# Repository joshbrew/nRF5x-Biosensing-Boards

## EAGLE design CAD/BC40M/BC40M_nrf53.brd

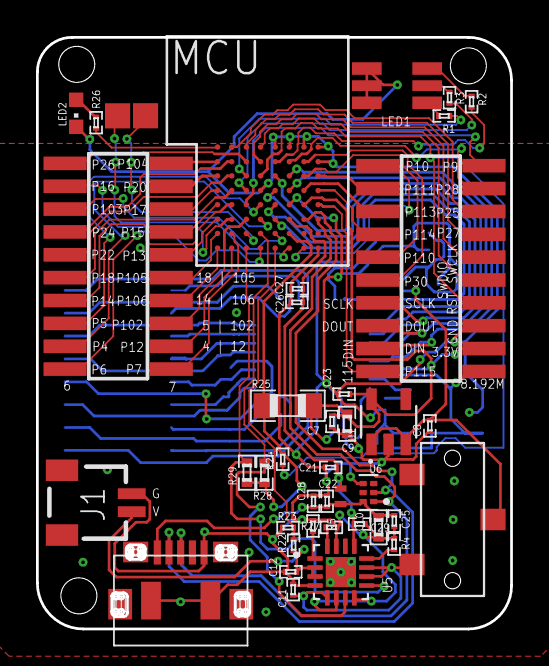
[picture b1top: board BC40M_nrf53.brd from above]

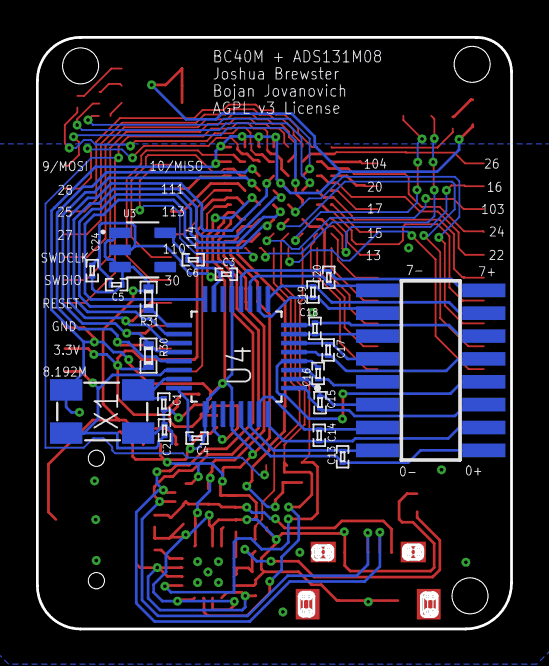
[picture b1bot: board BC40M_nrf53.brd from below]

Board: 2 copper layers, 26.3 x 32.9 mm, 62 parts (21 on the bottom side), 86 nets.

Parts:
C1, C2: 10pF; 0201
C3, C5, C6, C7, C8, C10, C24: 1uF; 0201
C4: 220nF; 0201
C9, C29: 10uF; 0402
C11, C12, C25, C26: 4.7uF; 0201
C13, C14, C15, C16, C17, C18, C19, C20: 100pF; 0201
C21, C23, C27, C28: 0.1uF; 0201
C22: 10nF; 0201
HDR1, HDR2: 1365-20
I1: 120Ω/500mAh; 0402_COILCRAFT
J1: SM02B-SRSS-TB(LF)(SN)
LED1: GM5WA94310A
LED2: CHIPLED_0603
MCU: BC40M
NFC1, NFC2: TPTP14SQ; TP14SQ
R1, R2, R3, R26: 3.3kΩ; 0201
R4: 1.18kΩ; 0201
R5: 1.13kΩ; 0201
R22: 348kΩ; 0201
R23: 750kΩ; 0201
R24: 100kΩ; 0201
R25: 0Ω; 0805
R27: 10kΩ; 0201
R28, R29: 10kΩ; 0402
R30, R31: 100kΩ; 0402
S1: CL-SB-12B-01T; CL-SB-12B
U1, U3: LP5907MFX-3.3/NOPB; SOT95P280X145-5N
U2: DX4R005JJ2R1800
U4: ADS131M08IPBS; QFP50P700X700X120-32N
U5: BQ24072RGTR; QFN50P300X300X100-17N
U6: TPD4S012DRYR; PSON50P145X100X60-6N
X1: ABM3B-8.000MHZ-B2-T
X5: 1365-16

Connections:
0N: C13.2, U4.30, X5.2
0P: C13.1, U4.29, X5.1
1N: C14.2, U4.31, X5.4
1P: C14.1, U4.32, X5.3
2N: C15.2, U4.2, X5.6
2P: C15.1, U4.1, X5.5
3N: C16.2, U4.3, X5.8
3P: C16.1, U4.4, X5.7
4N: C17.2, U4.6, X5.10
4P: C17.1, U4.5, X5.9
5N: C18.2, U4.7, X5.12
5P: C18.1, U4.8, X5.11
6N: C19.2, U4.10, X5.14
6P: C19.1, U4.9, X5.13
7N: C20.2, U4.11, X5.16
7P: C20.1, U4.12, X5.15
+5V: C22.2, C25.2, C28.2, C29.2, I1.P$2, U2.1, U6.6
+5V_ISO: C10.2, C21.1, C26.2, C27.2, I1.P$1, MCU.F5, U5.13
AVDD: C3.2, C6.1, U3.5, U4.15
BAT: C12.2, J1.2, R22.1, U5.2, U5.3
CAP: C4.1, U4.24
CHG: MCU.C7, R29.2, U5.9
CLKIN: C1.1, U4.23, X1.1
CLKOUT: C2.1, HDR2.20, U4.22, X1.3
CS: MCU.E4, R31.1, U4.17
CUR_DETECT: MCU.E7, R22.2, R23.1
D+: MCU.H5, U2.3, U6.1
D-: MCU.G5, U2.2, U6.2
DIN: HDR2.17, MCU.F2, U4.21
DOUT: HDR2.15, MCU.F3, R30.1, U4.20
DRDY: MCU.E3, U4.18
GND: C1.2, C2.2, C3.1, C4.2, C5.2, C6.2, C7.1, C8.1, C9.1, C10.1, C11.1, C12.1, C21.2, C22.1, C23.1, C24.1, C25.1, C26.1, C27.1, C28.1, C29.1, HDR2.16, J1.1, LED1.4, LED1.5, LED1.6, LED2.C, MCU.D3, MCU.E0, MCU.F0, MCU.F4, MCU.G0, MCU.H0, MCU.H1, MCU.H7, R4.1, R5.1, R23.2, R27.1, U1.2, U2.5, U2.MP1, U2.MP2, U3.2, U4.13, U4.25, U4.28, U5.4, U5.6, U5.8, U5.15, U6.4, X1.2, X1.4
ILM: R4.2, U5.12
ISET: R5.2, U5.16
LED5: LED2.A, R26.2
unnamed: LED1.2, R3.2
unnamed: LED1.3, R2.2
unnamed: LED1.1, R1.2
NFC1: MCU.F7, NFC2.TP
NFC2: MCU.C6, NFC1.TP
P4_AIN0: HDR1.17, MCU.D5
P5_AIN1: HDR1.15, MCU.D4
P6_AIN2: HDR1.19, MCU.D7
P7_AIN3: HDR1.20, MCU.B6
P9_MOSI: HDR2.2, MCU.C4
P10_MISO: HDR2.1, MCU.G7
P12: HDR1.18, MCU.B7
P13: HDR1.10, MCU.A5
P14: HDR1.13, MCU.B4
P15: HDR1.8, MCU.A4
P16: HDR1.3, MCU.B5
P17: HDR1.6, MCU.A3
P18: HDR1.11, MCU.B3
P19: MCU.C3, R3.1
P20: HDR1.4, MCU.A2
P21: MCU.C2, R1.1
P22: HDR1.9, MCU.B2
P24: HDR1.7, MCU.B1
P25_AIN4: HDR2.6, MCU.B0
P26_AIN5: HDR1.1, MCU.C1
P27_AIN6: HDR2.8, MCU.C0
P28_AIN7: HDR2.4, MCU.F1
P29: MCU.E1, R2.1
P30: HDR2.11, MCU.G1
P102: HDR1.16, MCU.C5
P103: HDR1.5, MCU.E6
P104: HDR1.2, MCU.A1
P105: HDR1.12, MCU.A6
P106: HDR1.14, MCU.A7
P109: MCU.A0, R26.1
P110: HDR2.9, MCU.G2
P111: HDR2.3, MCU.H2
P113: HDR2.5, MCU.G3
P114: HDR2.7, MCU.H3
P115: HDR2.19, MCU.H4
PGOOD: MCU.D6, R28.2, U5.7
RESET: HDR2.14, MCU.D2, R24.1
SCLK: HDR2.13, MCU.E2, U4.19
SWDCLK: HDR2.10, MCU.D1
SWDIO: HDR2.12, MCU.D0
SYNC/RESET: MCU.E5, U4.16
TS: R27.2, U5.1
VDD: C7.2, C9.2, C23.2, HDR2.18, MCU.G4, R25.2, R30.2, U1.5, U4.26
VDDH: MCU.F6, R24.2, R25.1, R28.1, R29.1
VIN: C5.1, C8.2, C24.2, R31.2, S1.2, U1.1, U1.3, U3.1, U3.3
VSWITCH: C11.2, S1.3, U5.5, U5.10, U5.11

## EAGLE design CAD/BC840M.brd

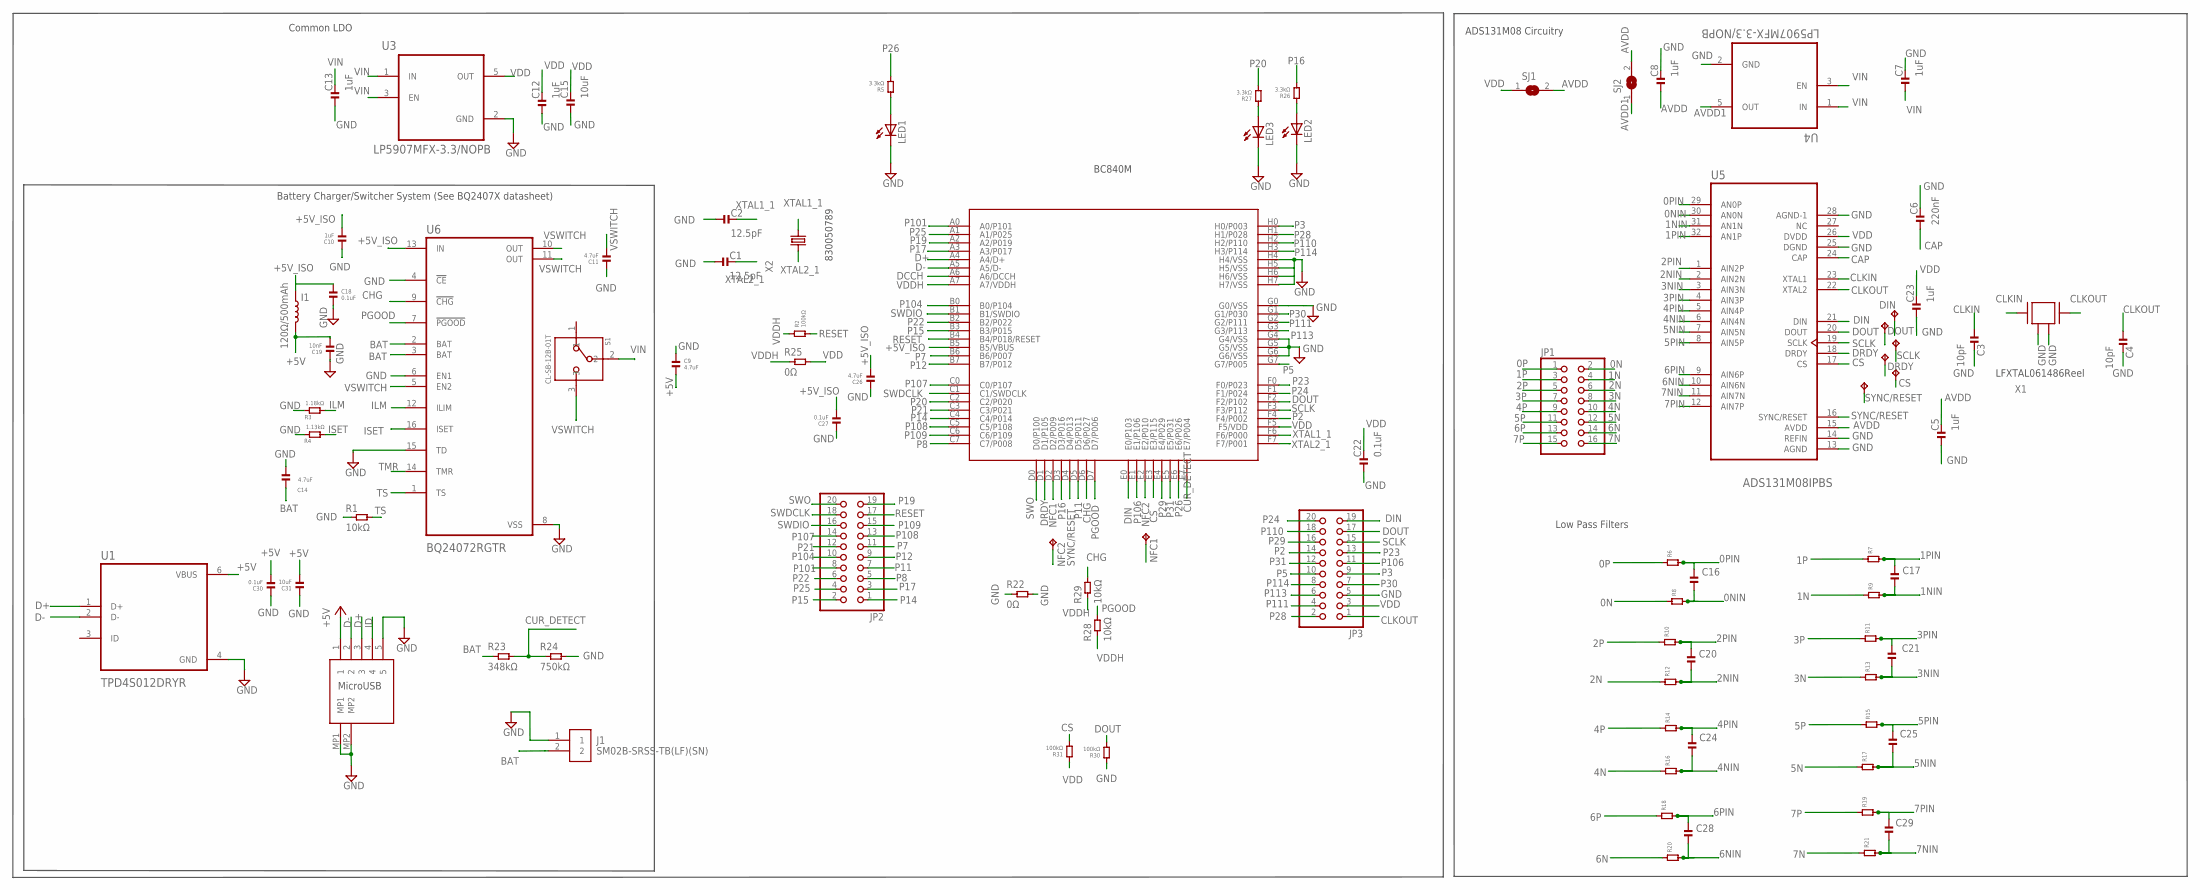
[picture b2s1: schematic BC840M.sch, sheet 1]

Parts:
C1, C2: 12.5pF; 0201
C3, C4: 10pF; 0201
C5, C7, C8, C10, C12, C13, C23: 1uF; 0201
C6: 220nF; 0201
C9, C11, C14, C26: 4.7uF; 0201
C15, C31: 10uF; 0402
C16, C17, C20, C21, C24, C25, C28, C29: 100pF; 0603
C18, C22, C27, C30: 0.1uF; 0201
C19: 10nF; 0201
CS: TPTP07R; TP07R
DIN: TPTP07R; TP07R
DOUT: TPTP07R; TP07R
DRDY: TPTP07R; TP07R
I1: 120Ω/500mAh; 0402_COILCRAFT
J1: SM02B-SRSS-TB(LF)(SN)
JP1: PINHD-2X8SMT; 2X08_SMT
JP2, JP3: PINHD-2X10SMT; 2X10_SMT
LED1, LED2, LED3: LEDCHIPLED_0603; CHIPLED_0603
NFC1, NFC2: TPTP14SQ; TP14SQ
R1: 10kΩ; 0201
R2: 100kΩ; 0201
R3: 1.18kΩ; 0603
R4: 1.13kΩ; 0603
R5, R26, R27: 3.3kΩ; 0201
R6, R7, R8, R9, R10, R11, R12, R13, R14, R15, R16, R17, R18, R19, R20, R21: 1MOhm; 0603
R22, R25: 0Ω; 0805
R23: 348kΩ; 0603
R24: 750kΩ; 0603
R28, R29: 10kΩ; 0402
R30, R31: 100kΩ; 0402
S1: CL-SB-12B-01T; CL-SB-12B
SCLK: TPTP07R; TP07R
SJ1, SJ2: SJ
SYNC: TPTP07R; TP07R
U1: TPD4S012DRYR; PSON50P145X100X60-6N
U2: BC840M
U3, U4: LP5907MFX-3.3/NOPB; SOT95P280X145-5N
U5: ADS131M08IPBS; QFP50P700X700X120-32N
U6: BQ24072RGTR; QFN50P300X300X100-17N
U7: DX4R005JJ2R1800
X1: ABM3B-8.000MHZ-B2-T
X2: FC-12M

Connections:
0N: JP1.2, R8.1
0NIN: C16.2, R8.2, U5.30 (AN0N)
0P: JP1.1, R6.1
0PIN: C16.1, R6.2, U5.29 (AN0P)
1N: JP1.4, R9.1
1NIN: C17.2, R9.2, U5.31 (AN1N)
1P: JP1.3, R7.1
1PIN: C17.1, R7.2, U5.32 (AN1P)
2N: JP1.6, R12.1
2NIN: C20.2, R12.2, U5.2 (AIN2N)
2P: JP1.5, R10.1
2PIN: C20.1, R10.2, U5.1 (AIN2P)
3N: JP1.8, R13.1
3NIN: C21.2, R13.2, U5.3 (AIN3N)
3P: JP1.7, R11.1
3PIN: C21.1, R11.2, U5.4 (AIN3P)
4N: JP1.10, R16.1
4NIN: C24.2, R16.2, U5.6 (AIN4N)
4P: JP1.9, R14.1
4PIN: C24.1, R14.2, U5.5 (AIN4P)
5N: JP1.12, R17.1
5NIN: C25.2, R17.2, U5.7 (AIN5N)
5P: JP1.11, R15.1
5PIN: C25.1, R15.2, U5.8 (AIN5P)
6N: JP1.14, R20.1
6NIN: C28.2, R20.2, U5.10 (AIN6N)
6P: JP1.13, R18.1
6PIN: C28.1, R18.2, U5.9 (AIN6P)
7N: JP1.16, R21.1
7NIN: C29.2, R21.2, U5.11 (AIN7N)
7P: JP1.15, R19.1
7PIN: C29.1, R19.2, U5.12 (AIN7P)
+5V: C9.2, C19.2, C30.2, C31.2, I1.P$2 (2), U1.6 (VBUS), U7.1
+5V_ISO: C10.2, C18.1, C26.2, C27.2, I1.P$1 (1), U2.B5 (B5/VBUS), U6.13 (IN)
AVDD: C5.2, C8.1, SJ1.2, SJ2.2, U5.15 (AVDD)
AVDD1: SJ2.1, U4.5 (OUT)
BAT: C14.2, J1.2, R23.1, U6.2 (BAT), U6.3 (BAT)
CAP: C6.1, U5.24 (CAP)
CHG: R29.2, U2.D6 (D6/P027), U6.9 (!CHG)
CLKIN: C3.1, U5.23 (XTAL1), X1.1
CLKOUT: C4.1, JP3.1, U5.22 (XTAL2), X1.3
CS: CS.TP, R31.1, U2.E3 (E3/P115), U5.17 (CS)
CUR_DETECT: R23.2, R24.1, U2.E7 (E7/P004)
D+: U1.1 (D+), U2.A4 (A4/D+), U7.3
D-: U1.2 (D-), U2.A5 (A5/D-), U7.2
DCCH: U2.A6 (A6/DCCH)
DIN: DIN.TP, JP3.19, U2.E0 (E0/P103), U5.21 (DIN)
DOUT: DOUT.TP, JP3.17, R30.1, U2.F2 (F2/P102), U5.20 (DOUT)
DRDY: DRDY.TP, U2.D1 (D1/P105), U5.18 (DRDY)
GND: C1.1, C2.1, C3.2, C4.2, C5.1, C6.2, C7.2, C8.2, C9.1, C10.1, C11.1, C12.1, C13.1, C14.1, C15.1, C18.2, C19.1, C22.1, C23.1, C26.1, C27.1, C30.1, C31.1, J1.1, JP3.5, LED1.C, LED2.C, LED3.C, R1.1, R3.1, R4.1, R22.1, R22.2, R24.2, R30.2, U1.4 (GND), U2.G0 (G0/VSS), U2.G4 (G4/VSS), U2.G5 (G5/VSS), U2.G6 (G6/VSS), U2.H4 (H4/VSS), U2.H5 (H5/VSS), U2.H6 (H6/VSS), U2.H7 (H7/VSS), U3.2 (GND), U4.2 (GND), U5.13 (AGND), U5.14 (REFIN), U5.25 (DGND), U5.28 (AGND-1), U6.4 (!CE), U6.6 (EN1), U6.8 (VSS), U6.15 (TD), U7.5, U7.MP1, U7.MP2, X1.2, X1.4
ID: U7.4
ILM: R3.2, U6.12 (ILIM)
ISET: R4.2, U6.16 (ISET)
LED1: LED1.A, R5.2
LED2: LED2.A, R26.2
LED3: LED3.A, R27.2
NFC1: NFC2.TP, U2.D2 (D2/P009)
NFC2: NFC1.TP, U2.E2 (E2/P010)
P2: JP3.14, U2.F4 (F4/P002)
P3: JP3.9, U2.H0 (H0/P003)
P5: JP3.10, U2.G7 (G7/P005)
P7: JP2.11, U2.B6 (B6/P007)
P8: JP2.5, U2.C7 (C7/P008)
P11: JP2.7, U2.D5 (D5/P011)
P12: JP2.9, U2.B7 (B7/P012)
P14: JP2.1, U2.C4 (C4/P014)
P15: JP2.2, U2.B3 (B3/P015)
P16: R26.1, U2.D3 (D3/P016)
P17: JP2.3, U2.A3 (A3/P017)
P19: JP2.19, U2.A2 (A2/P019)
P20: R27.1, U2.C2 (C2/P020)
P21: JP2.12, U2.C3 (C3/P021)
P22: JP2.6, U2.B2 (B2/P022)
P23: JP3.13, U2.F0 (F0/P023)
P24: JP3.20, U2.F1 (F1/P024)
P25: JP2.4, U2.A1 (A1/P025)
P26: R5.1, U2.E6 (E6/P026)
P28: JP3.2, U2.H1 (H1/P028)
P29: JP3.16, U2.E4 (E4/P029)
P30: JP3.7, U2.G1 (G1/P030)
P31: JP3.12, U2.E5 (E5/P031)
P101: JP2.8, U2.A0 (A0/P101)
P104: JP2.10, U2.B0 (B0/P104)
P106: JP3.11, U2.E1 (E1/P106)
P107: JP2.14, U2.C0 (C0/P107)
P108: JP2.13, U2.C5 (C5/P108)
P109: JP2.15, U2.C6 (C6/P109)
P110: JP3.18, U2.H2 (H2/P110)
P111: JP3.4, U2.G2 (G2/P111)
P113: JP3.6, U2.G3 (G3/P113)
P114: JP3.8, U2.H3 (H3/P114)
PGOOD: R28.2, U2.D7 (D7/P006), U6.7 (!PGOOD)
RESET: JP2.17, R2.1, U2.B4 (B4/P018/RESET)
SCLK: JP3.15, SCLK.TP, U2.F3 (F3/P112), U5.19 (SCLK)
SWDCLK: JP2.18, U2.C1 (C1/SWDCLK)
SWDIO: JP2.16, U2.B1 (B1/SWDIO)
SWO: JP2.20, U2.D0 (D0/P100)
SYNC/RESET: SYNC.TP, U2.D4 (D4/P013), U5.16 (SYNC/RESET)
TMR: U6.14 (TMR)
TS: R1.2, U6.1 (TS)
VDD: C12.2, C15.2, C22.2, C23.2, JP3.3, R25.2, R31.2, SJ1.1, U2.F5 (F5/VDD), U3.5 (OUT), U5.26 (DVDD)
VDDH: R2.2, R25.1, R28.1, R29.1, U2.A7 (A7/VDDH)
VIN: C7.1, C13.2, S1.2, U3.1 (IN), U3.3 (EN), U4.1 (IN), U4.3 (EN)
VSWITCH: C11.2, S1.3, U6.5 (EN2), U6.10 (OUT), U6.11 (OUT)
XTAL1_1: C2.2, U2.F6 (F6/P000), X2.2
XTAL2_1: C1.2, U2.F7 (F7/P001), X2.1

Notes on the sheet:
LFXTAL061486Reel
830050789
MicroUSB
Battery Charger/Switcher System (See BQ2407X datasheet)
ADS131M08 Circuitry
Common LDO
BC840M
Low Pass Filters

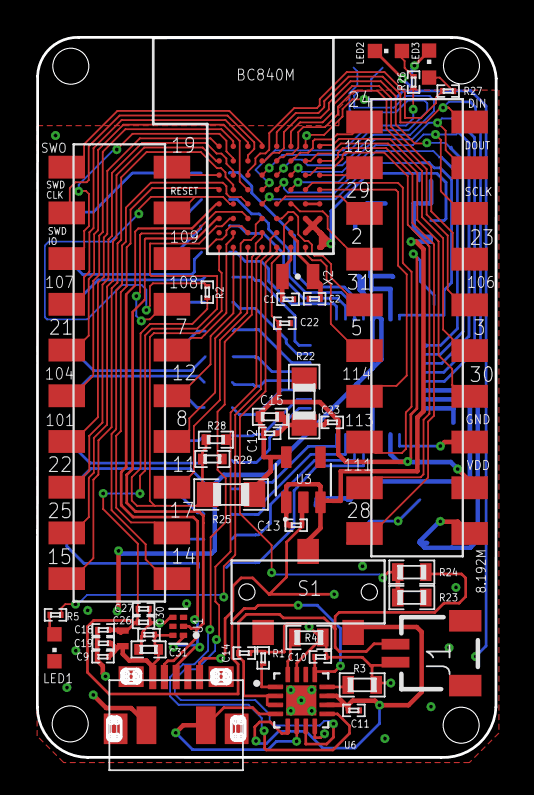
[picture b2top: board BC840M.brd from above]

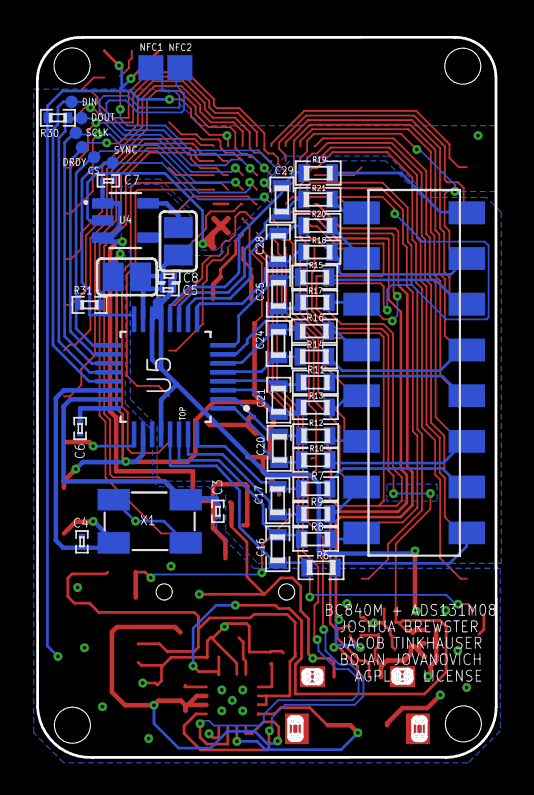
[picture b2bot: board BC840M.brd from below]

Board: 2 copper layers, 25.5 x 40.0 mm, 90 parts (46 on the bottom side), 103 nets.

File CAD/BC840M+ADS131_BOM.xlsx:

Designators | Ct | Part # | Description | Substitutes | Cost | 1.0 | 10.0 | 100.0 | 1000.0
U1 | 1.0 | TPD4S012DRYR | TVS Diodes |  |  | 0.73 | 6.48 | 49.7 | 314.0
U2 | 1.0 | BC840M | Fanstel Microcontroller |  | From Fanstel: | 8.86 | 84.9 | 812.0 | 7380.0
U3,U4 | 2.0 | LP5907-3.3MFX | 3v3 LDO | Stock (moq 155) |  | 0.7 | 5.93 | 41.1 | 269.0
U5 | 1.0 | ADS131M08IPBS | ADC 24bit 8ch |  | From TI: | 7.739 | 77.39 | 630.9 | 4206
U6 | 1.0 | BQ24076RGTR | Battery charge/switch interface | BQ2407xRGTR |  | 2.52 | 22.7 | 183.0 | 1250.0
U7 | 1.0 | DX4R005JJ2R1800 | MicroUSB port |  |  | 0.79 | 6.32 | 54.9 | 386.0
S1 | 1.0 | CL-SB-12B-01T | Switch On-Off | Alt part/source |  | 0.93 | 8.37 | 66.1 | 533.0
X1 | 1.0 | LFXTAL061486Reel | 8.192Mhz Crystal |  |  | 0.92 | 7.63 | 67.5 | 516.0
X2 | 1.0 | 8.30105946101E11 | 32.7680 Crystal |  |  | 0.67 | 6.11 | 52.4 | 524
I1 | 1.0 | MMZ1005S121CT000 | 120Ohm/500mAh 0402 INDUCTOR |  |  | 0.1 | 0.54 | 2.9 | 23.0
C1,C2 | 2.0 | CC0201DRNPO9BN7R0 | 7pF 0201 MLCC |  |  | 0.1 | 0.37 | 1.8 | 10.0
C3,C4, | 2.0 | 02015A100JAT2A | 10pF 0201 MLCC |  |  | 0.1 | 0.37 | 1.8 | 10.0
C5,C7,C8,C10,C12,C13,C23 | 7.0 | 02016D224KAT2A | 1uF 0201 MLCC |  |  | 0.1 | 0.37 | 1.8 | 10.0
C6 | 1.0 | 02016D224KAT2A | 220nF 0201 MLCC |  |  | 0.1 | 0.37 | 1.8 | 10.0
C9,C11,C14,C26 | 4.0 | AMK063EBJ475MP-F | 4.7uF 0201 MLCC |  |  | 0.1 | 0.37 | 1.8 | 10.0
C15,C31 | 2.0 | 0402YG104ZAT4A | 10uF 0402 MLCC |  |  | 0.1 | 0.37 | 1.8 | 10.0
C18,C22,C27,C30 | 4.0 | 0201ZD104KAT2A | 0.1uF 0201 MLCC |  |  | 0.1 | 0.37 | 1.8 | 10.0
C19 | 1.0 | 0201YD103KAT4A | 10nF 0201 MLCC |  |  | 0.1 | 0.37 | 1.8 | 10.0
C16,C17,C20,C21,C24,C25,C28,C29 | 8.0 | 06035A101JAT4A | 100pF 0603 MLCC | 1uF 0603 MLCC |  | 0.1 | 0.37 | 1.8 | 10.0
R6,R7,R8,R9,R10,R11,R12,R13,R1,R15,R16,R17,R18,R19,R20 | 16.0 | AC0603JR-071ML | 1MOhm 0603 RESISTOR | 100k 0603 RESISTOR |  | 0.1 | 0.2 | 4.8 | 8.0
R1 | 1.0 | CRCW020110K0JNED | 10KOhm 0201 RESISTOR |  |  | 0.1 | 0.2 | 4.8 | 8.0
R28, R29 | 2.0 | AC0402FR-0710KL | 10KOhm 0402 RESISTOR |  |  | 0.1 | 0.2 | 4.8 | 8.0
R2 | 1.0 | CRCW0201100KFNED | 100KOhm 0201 RESISTOR |  |  | 0.1 | 0.2 | 4.8 | 8.0
R30,R31 | 2.0 | AC0402FR-13100KL | 100KOhm 0402 RESISTOR |  |  | 0.1 | 0.2 | 4.8 | 8.0
R23 | 1.0 | RC0603FR-07348KL | 348KOhm 0603 RESISTOR |  |  | 0.1 | 0.2 | 4.8 | 8.0
R24 | 1.0 | CR0603-FX-7503ELF | 750KOhm 0603 RESISTOR |  |  | 0.1 | 0.2 | 4.8 | 8.0
R5,R26,R27 | 3.0 | RC0201FR-073K3L | 3.3KOhm 0201 RESISTOR |  |  | 0.1 | 0.2 | 4.8 | 8.0
R3 | 1.0 | RC0603FR-071K18L | 1.18KOhm 0603 RESISTOR |  |  | 0.1 | 0.2 | 4.8 | 8.0
R4 | 1.0 | CR0603-FX-1131ELF | 1.13KOhm 0603 RESISTOR |  |  | 0.1 | 0.2 | 4.8 | 8.0
R22,R25 | 2.0 | RC0805JR-070RL | 0Ohm 0805 RESISTOR |  |  | 0.1 | 0.2 | 4.8 | 8.0
JP1 | 1.0 | SSM-108-F-DV-K-TR | 2X8 SMT 2.54MM HEADER FEMALE |  |  | 3.75 | 36.0 | 300.0 | 2170.0
JP2,JP3 | 2.0 | SSM-110-F-DV-P-TR | 2X10 SMT 2.54MM HEADER FEMALE |  |  | 4.12 | 39.6 | 330.0 | 2390.0
LED1 | 1.0 | AA1608SESK | 0603 CHIPLED ORANGE |  |  | 0.48 | 2.81 | 16.2 | 127.0
LED2 | 1.0 | AA1608QBS/D-10MAV | 0603 CHIPLED BLUE |  |  | 0.48 | 2.81 | 16.2 | 127.0
LED3 | 1.0 | AA1608ZGSK-10MAV | 0603 CHIPLED GREEN |  |  | 0.46 | 2.96 | 22.8 | 151.0
J1 | 1.0 | SM02B-SRSS-TB(LF)(SN) | CONN HEADER SH 2POS 1MM |  | Win-Source: (moq 135) | 1.0 | 10.0 | 51.74 | 301.125
 |  |  |  |  |  | 36.249 | 326.08 | 2766.44 | 20845.125
 |  | SHR-02V-S | CONN HOUSING SH 2POS 1MM | Stock? or Stock? | Unit Cost | 36.249 | 32.608 | 27.6644 | 20.845125
 |  |  |  |  | W/out headers | 28.379 | 250.48 | 2136.44 | 16285.125
 |  |  |  |  | Unit Cost (not accurate) | 28.379 | 25.048 | 21.3644 | 16.285125

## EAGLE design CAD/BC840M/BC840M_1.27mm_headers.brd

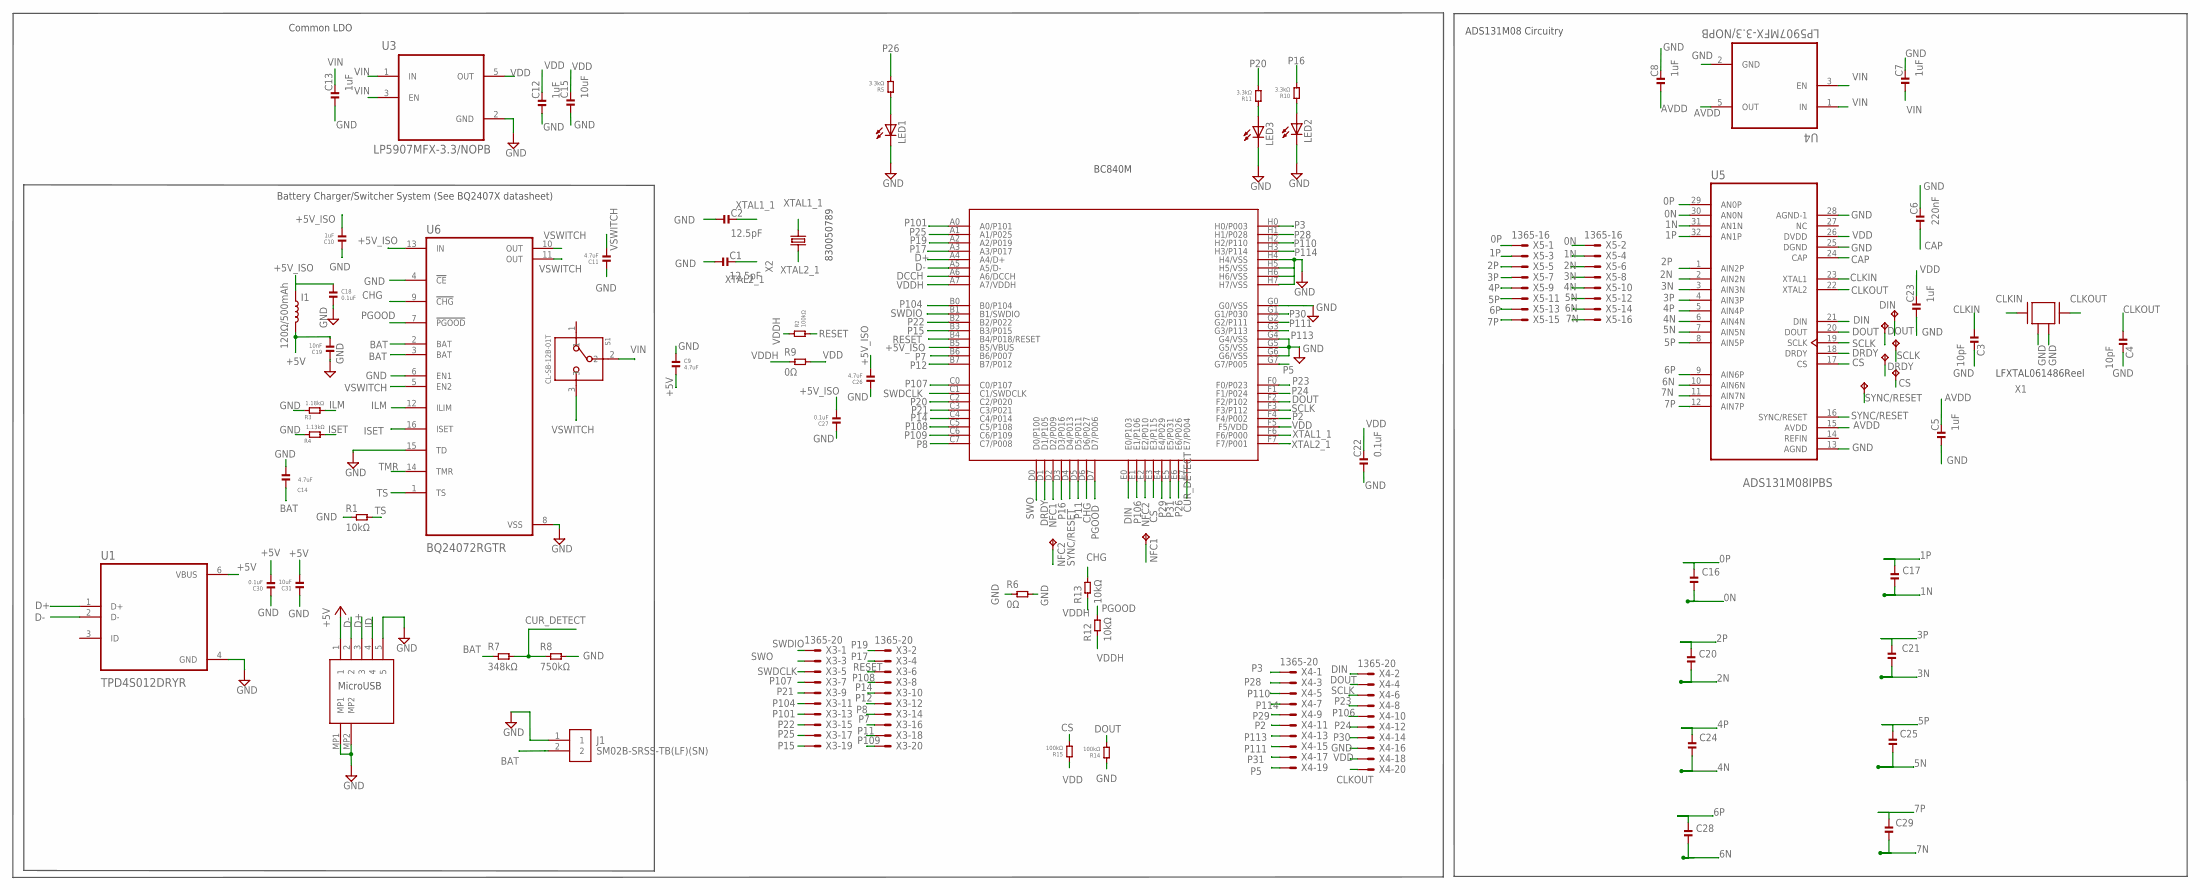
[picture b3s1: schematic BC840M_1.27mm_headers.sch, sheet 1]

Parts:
C1, C2: 12.5pF; 0201
C3, C4: 10pF; 0201
C5, C7, C8, C10, C12, C13, C23: 1uF; 0201
C6: 220nF; 0201
C9, C11, C14, C26: 4.7uF; 0201
C15, C31: 10uF; 0402
C16, C17, C20, C21, C24, C25, C28, C29: 100pF; 0201
C18, C22, C27, C30: 0.1uF; 0201
C19: 10nF; 0201
CS: TPTP07R; TP07R
DIN: TPTP07R; TP07R
DOUT: TPTP07R; TP07R
DRDY: TPTP07R; TP07R
I1: 120Ω/500mAh; 0402_COILCRAFT
J1: SM02B-SRSS-TB(LF)(SN)
LED1, LED2, LED3: LEDCHIPLED_0603; CHIPLED_0603
NFC1, NFC2: TPTP14SQ; TP14SQ
R1: 10kΩ; 0201
R2: 100kΩ; 0201
R3: 1.18kΩ; 0201
R4: 1.13kΩ; 0201
R5, R10, R11: 3.3kΩ; 0201
R6, R9: 0Ω; 0805
R7: 348kΩ; 0201
R8: 750kΩ; 0201
R12, R13: 10kΩ; 0402
R14, R15: 100kΩ; 0402
S1: CL-SB-12B-01T; CL-SB-12B
SCLK: TPTP07R; TP07R
SYNC: TPTP07R; TP07R
U1: TPD4S012DRYR; PSON50P145X100X60-6N
U2: BC840M
U3, U4: LP5907MFX-3.3/NOPB; SOT95P280X145-5N
U5: ADS131M08IPBS; QFP50P700X700X120-32N
U6: BQ24072RGTR; QFN50P300X300X100-17N
U7: DX4R005JJ2R1800
X1: ABM3B-8.000MHZ-B2-T
X2: FC-12M
X3, X4: 1365-20
X5: 1365-16

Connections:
0N: C16.2, U5.30 (AN0N), X5.2
0P: C16.1, U5.29 (AN0P), X5.1
1N: C17.2, U5.31 (AN1N), X5.4
1P: C17.1, U5.32 (AN1P), X5.3
2N: C20.2, U5.2 (AIN2N), X5.6
2P: C20.1, U5.1 (AIN2P), X5.5
3N: C21.2, U5.3 (AIN3N), X5.8
3P: C21.1, U5.4 (AIN3P), X5.7
4N: C24.2, U5.6 (AIN4N), X5.10
4P: C24.1, U5.5 (AIN4P), X5.9
5N: C25.2, U5.7 (AIN5N), X5.12
5P: C25.1, U5.8 (AIN5P), X5.11
6N: C28.2, U5.10 (AIN6N), X5.14
6P: C28.1, U5.9 (AIN6P), X5.13
7N: C29.2, U5.11 (AIN7N), X5.16
7P: C29.1, U5.12 (AIN7P), X5.15
+5V: C9.2, C19.2, C30.2, C31.2, I1.P$2 (2), U1.6 (VBUS), U7.1
+5V_ISO: C10.2, C18.1, C26.2, C27.2, I1.P$1 (1), U2.B5 (B5/VBUS), U6.13 (IN)
AVDD: C5.2, C8.1, U4.5 (OUT), U5.15 (AVDD)
BAT: C14.2, J1.2, R7.1, U6.2 (BAT), U6.3 (BAT)
CAP: C6.1, U5.24 (CAP)
CHG: R13.2, U2.D6 (D6/P027), U6.9 (!CHG)
CLKIN: C3.1, U5.23 (XTAL1), X1.1
CLKOUT: C4.1, U5.22 (XTAL2), X1.3, X4.20
CS: CS.TP, R15.1, U2.E3 (E3/P115), U5.17 (CS)
CUR_DETECT: R7.2, R8.1, U2.E7 (E7/P004)
D+: U1.1 (D+), U2.A4 (A4/D+), U7.3
D-: U1.2 (D-), U2.A5 (A5/D-), U7.2
DCCH: U2.A6 (A6/DCCH)
DIN: DIN.TP, U2.E0 (E0/P103), U5.21 (DIN), X4.2
DOUT: DOUT.TP, R14.1, U2.F2 (F2/P102), U5.20 (DOUT), X4.4
DRDY: DRDY.TP, U2.D1 (D1/P105), U5.18 (DRDY)
GND: C1.1, C2.1, C3.2, C4.2, C5.1, C6.2, C7.2, C8.2, C9.1, C10.1, C11.1, C12.1, C13.1, C14.1, C15.1, C18.2, C19.1, C22.1, C23.1, C26.1, C27.1, C30.1, C31.1, J1.1, LED1.C, LED2.C, LED3.C, R1.1, R3.1, R4.1, R6.1, R6.2, R8.2, R14.2, U1.4 (GND), U2.G0 (G0/VSS), U2.G4 (G4/VSS), U2.G5 (G5/VSS), U2.G6 (G6/VSS), U2.H4 (H4/VSS), U2.H5 (H5/VSS), U2.H6 (H6/VSS), U2.H7 (H7/VSS), U3.2 (GND), U4.2 (GND), U5.13 (AGND), U5.25 (DGND), U5.28 (AGND-1), U6.4 (!CE), U6.6 (EN1), U6.8 (VSS), U6.15 (TD), U7.5, U7.MP1, U7.MP2, X1.2, X1.4, X4.16
ID: U7.4
ILM: R3.2, U6.12 (ILIM)
ISET: R4.2, U6.16 (ISET)
LED1: LED1.A, R5.2
LED2: LED2.A, R10.2
LED3: LED3.A, R11.2
NFC1: NFC2.TP, U2.D2 (D2/P009)
NFC2: NFC1.TP, U2.E2 (E2/P010)
P2: U2.F4 (F4/P002), X4.11
P3: U2.H0 (H0/P003), X4.1
P5: U2.G7 (G7/P005), X4.19
P7: U2.B6 (B6/P007), X3.16
P8: U2.C7 (C7/P008), X3.14
P11: U2.D5 (D5/P011), X3.18
P12: U2.B7 (B7/P012), X3.12
P14: U2.C4 (C4/P014), X3.10
P15: U2.B3 (B3/P015), X3.19
P16: R10.1, U2.D3 (D3/P016)
P17: U2.A3 (A3/P017), X3.4
P19: U2.A2 (A2/P019), X3.2
P20: R11.1, U2.C2 (C2/P020)
P21: U2.C3 (C3/P021), X3.9
P22: U2.B2 (B2/P022), X3.15
P23: U2.F0 (F0/P023), X4.8
P24: U2.F1 (F1/P024), X4.12
P25: U2.A1 (A1/P025), X3.17
P26: R5.1, U2.E6 (E6/P026)
P28: U2.H1 (H1/P028), X4.3
P29: U2.E4 (E4/P029), X4.9
P30: U2.G1 (G1/P030), X4.14
P31: U2.E5 (E5/P031), X4.17
P101: U2.A0 (A0/P101), X3.13
P104: U2.B0 (B0/P104), X3.11
P106: U2.E1 (E1/P106), X4.10
P107: U2.C0 (C0/P107), X3.7
P108: U2.C5 (C5/P108), X3.8
P109: U2.C6 (C6/P109), X3.20
P110: U2.H2 (H2/P110), X4.5
P111: U2.G2 (G2/P111), X4.15
P113: U2.G3 (G3/P113), X4.13
P114: U2.H3 (H3/P114), X4.7
PGOOD: R12.2, U2.D7 (D7/P006), U6.7 (!PGOOD)
RESET: R2.1, U2.B4 (B4/P018/RESET), X3.6
SCLK: SCLK.TP, U2.F3 (F3/P112), U5.19 (SCLK), X4.6
SWDCLK: U2.C1 (C1/SWDCLK), X3.5
SWDIO: U2.B1 (B1/SWDIO), X3.1
SWO: U2.D0 (D0/P100), X3.3
SYNC/RESET: SYNC.TP, U2.D4 (D4/P013), U5.16 (SYNC/RESET)
TMR: U6.14 (TMR)
TS: R1.2, U6.1 (TS)
VDD: C12.2, C15.2, C22.2, C23.2, R9.2, R15.2, U2.F5 (F5/VDD), U3.5 (OUT), U5.26 (DVDD), X4.18
VDDH: R2.2, R9.1, R12.1, R13.1, U2.A7 (A7/VDDH)
VIN: C7.1, C13.2, S1.2, U3.1 (IN), U3.3 (EN), U4.1 (IN), U4.3 (EN)
VSWITCH: C11.2, S1.3, U6.5 (EN2), U6.10 (OUT), U6.11 (OUT)
XTAL1_1: C2.2, U2.F6 (F6/P000), X2.2
XTAL2_1: C1.2, U2.F7 (F7/P001), X2.1

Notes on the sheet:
LFXTAL061486Reel
830050789
MicroUSB
Battery Charger/Switcher System (See BQ2407X datasheet)
ADS131M08 Circuitry
Common LDO
BC840M

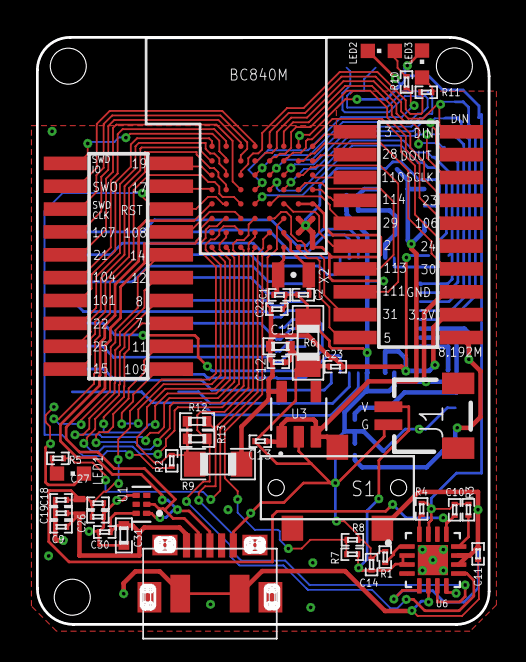
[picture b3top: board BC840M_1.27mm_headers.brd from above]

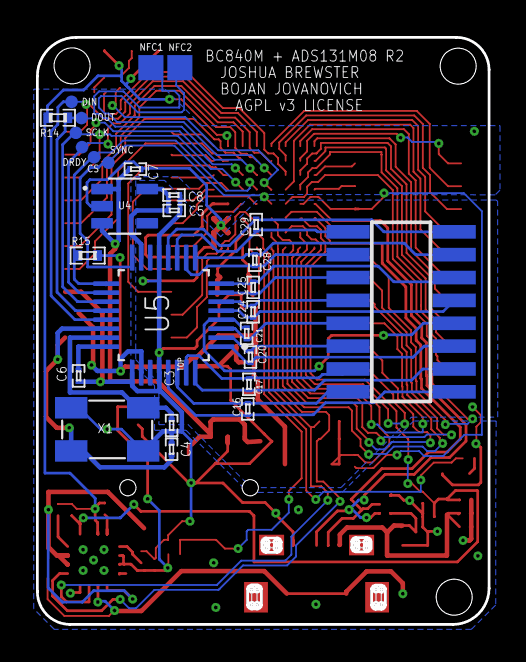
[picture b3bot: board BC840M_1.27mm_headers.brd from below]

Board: 2 copper layers, 25.1 x 32.6 mm, 72 parts (28 on the bottom side), 86 nets.

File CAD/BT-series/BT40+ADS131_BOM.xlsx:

Designators | Ct | Part # | Description | Substitutes | NOTES | Costs (old) | 1.0 | 10.0 | 100.0 | 1000.0
U1 | 1.0 | TPD4S012DRYR | TVS Diodes |  |  |  | 0.73 | 6.48 | 49.7 | 314.0
U2 | 1.0 | BT40 | Fanstel Microcontroller | BT840, BT832, BT832A, or variants (F, E, X, XE) | Prefer BT40 (nRF53) | From Fanstel: | 10.41 | 99.8 | 998.0 | 7650.0
U3,U4 | 2.0 | LP5907-3.3MFX | 3v3 LDO | Alt Stock (moq 155) |  |  | 0.7 | 5.93 | 41.1 | 269.0
U5 | 1.0 | ADS131M08IPBS | ADC 24bit 8ch |  |  | From TI: | 7.739 | 77.39 | 630.9 | 4206
U6 | 1.0 | BQ24076RGTR | Battery charge/switch interface | BQ2407xRGTR |  |  | 2.52 | 22.7 | 183.0 | 1250.0
U7 | 1.0 | DX4R005JJ2R1800 | MicroUSB port |  |  |  | 0.79 | 6.32 | 54.9 | 386.0
S1 | 1.0 | CL-SB-12B-01T | Switch On-Off | Alt part/source |  |  | 0.93 | 8.37 | 66.1 | 533.0
X1 | 1.0 | LFXTAL061486Reel | 8.192Mhz Crystal |  |  |  | 0.92 | 7.63 | 67.5 | 516.0
X2 | 1.0 | 8.30105946101E11 | 32.7680 Crystal |  |  |  | 0.67 | 6.11 | 52.4 | 524
I1 | 1.0 | MMZ1005S121CT000 | 120Ohm/500mAh 0402 INDUCTOR |  |  |  | 0.1 | 0.54 | 2.9 | 23.0
C1,C2 | 2.0 | CC0201DRNPO9BN7R0 | 7pF 0201 MLCC |  |  |  | 0.2 | 0.37 | 1.8 | 10.0
C3,C4, | 2.0 | 02015A100JAT2A | 10pF 0201 MLCC |  |  |  | 0.2 | 0.37 | 1.8 | 10.0
C5,C7,C8,C10,C12,C13,C23 | 7.0 | 02016D224KAT2A | 1uF 0201 MLCC |  |  |  | 0.7 | 0.37 | 1.8 | 10.0
C6 | 1.0 | 02016D224KAT2A | 220nF 0201 MLCC |  |  |  | 0.1 | 0.37 | 1.8 | 10.0
C9,C11,C14,C26 | 4.0 | AMK063EBJ475MP-F | 4.7uF 0201 MLCC |  |  |  | 0.4 | 1.48 | 7.2 | 40
C15,C31 | 2.0 | 0402YG104ZAT4A | 10uF 0402 MLCC |  |  |  | 0.2 | 0.74 | 3.6 | 20
C18,C22,C27,C30 | 4.0 | 0201ZD104KAT2A | 0.1uF 0201 MLCC |  |  |  | 0.4 | 1.48 | 7.2 | 40
C19 | 1.0 | 0201YD103KAT4A | 10nF 0201 MLCC |  |  |  | 0.8 | 2.96 | 14.4 | 80
C16,C17,C20,C21,C24,C25,C28,C29 | 8.0 | 02013C101KAT2A | 100pF 0201 MLCC |  |  |  | 0.1 | 0.37 | 1.8 | 10.0
R1 | 1.0 | CRCW020110K0JNED | 10KOhm 0201 RESISTOR |  |  |  | 0.2 | 0.2 | 4.8 | 8.0
R10, R11 | 2.0 | AC0402FR-0710KL | 10KOhm 0402 RESISTOR |  |  |  | 0.1 | 0.2 | 4.8 | 8.0
R2 | 1.0 | CRCW0201100KFNED | 100KOhm 0201 RESISTOR |  |  |  | 0.1 | 0.2 | 4.8 | 8.0
R12,R13 | 2.0 | AC0402FR-13100KL | 100KOhm 0402 RESISTOR |  |  |  | 0.1 | 0.2 | 4.8 | 8.0
R6 | 1.0 | RC0201FR-07348KL | 348KOhm 0201 RESISTOR |  |  |  | 0.1 | 0.2 | 4.8 | 8.0
R7 | 1.0 | RC0201FR-07750KL | 750KOhm 0201 RESISTOR |  |  |  | 0.1 | 0.2 | 4.8 | 8.0
R5,R8,R9 | 3.0 | RC0201FR-073K3L | 3.3KOhm 0201 RESISTOR |  |  |  | 0.1 | 0.2 | 4.8 | 8.0
R3 | 1.0 | RC0201FR-071K18L | 1.18KOhm 0201 RESISTOR |  |  |  | 0.1 | 0.2 | 4.8 | 8.0
R4 | 1.0 | ERJ-1GNF1131C | 1.13KOhm 0201 RESISTOR |  |  |  | 0.1 | 0.2 | 4.8 | 8.0
JP1 | 1.0 | NPTC082KFMS-RC | 2X8 SMT 1.25MM HEADER FEMALE |  |  |  | 1.89 | 16.41 | 146.66 | 1047.6
JP2,JP3 | 2.0 | NPTC102KFMS-RC | 2X10 SMT 1.25MM HEADER FEMALE
LED1 | 1.0 | AA1608SESK | 0603 CHIPLED ORANGE |  |  |  | 0.48 | 2.81 | 16.2 | 127.0
LED2 | 1.0 | AA1608QBS/D-10MAV | 0603 CHIPLED BLUE |  |  |  | 0.48 | 2.81 | 16.2 | 127.0
LED3 | 1.0 | AA1608ZGSK-10MAV | 0603 CHIPLED GREEN |  |  |  | 0.46 | 2.96 | 22.8 | 151.0
J1 | 1.0 | SM02B-SRSS-TB(LF)(SN) | CONN HEADER SH 2POS 1MM
total | 62 |  |  |  |  |  | 32.919 | 276.57 | 2432.96 | 17425.6
 |  |  | CONN HOUSING JST-SH 2POS 1MM | Stock? or Stock? |  | Unit Cost | 32.919 | 27.657 | 24.3296 | 17.4256
 |  |  |  |  |  | Does not include battery, and peripherals
 |  |  |  |  |  | W/out headers | 31.029 | 260.16 | 2286.3 | 16378
 |  |  |  |  |  | Unit Cost | 31.029 | 26.016 | 22.863 | 16.378
 |  |  |  |  |  | Unit cost w/ Battery, figure $2.50 per | 35.419 | 30.157 | 26.8296 | 19.9256
 |  |  |  |  |  | Add Peripherals, ~$9 off Aliexpress | 44.419 | 39.157 | 35.8296 | 28.9256
 |  |  |  |  |  | Add PCBWay PCBs | 48.419 | 43.157 | 36.9596 | 29.3256 | Cost for 200 boards: 226. Minimum 10, board cost for 1000 estimated from online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
 |  |  |  |  |  | Add Portland assembly cost (lowest) | 270.889 | 154.392 | 67.0296 | 50.2856 | 5 minimum
 |  |  |  |  |  | Add the plastic band and flex connector?

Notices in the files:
CAD/BC40M/BC40M_nrf53.brd:
AGPL v3 License
CAD/BM832A.brd:
MIT LICENSE
parts and their libraries:
spkfncoils: Licensing: Creative Commons ShareAlike 4.0 International - https://creativecommons.org/licenses/by-sa/4.0
ads131m08irsnr: COPYRIGHT: Copyright (C) 2022 Ultra Librarian. All rights reserved.
COPYRIGHT: Copyright (C) 2016 Accelerated Designs. All rights reserved
